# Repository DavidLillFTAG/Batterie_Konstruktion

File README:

Testfile
<<<<<<< HEAD
123456

=======
123
123123
>>>>>>> dev_david

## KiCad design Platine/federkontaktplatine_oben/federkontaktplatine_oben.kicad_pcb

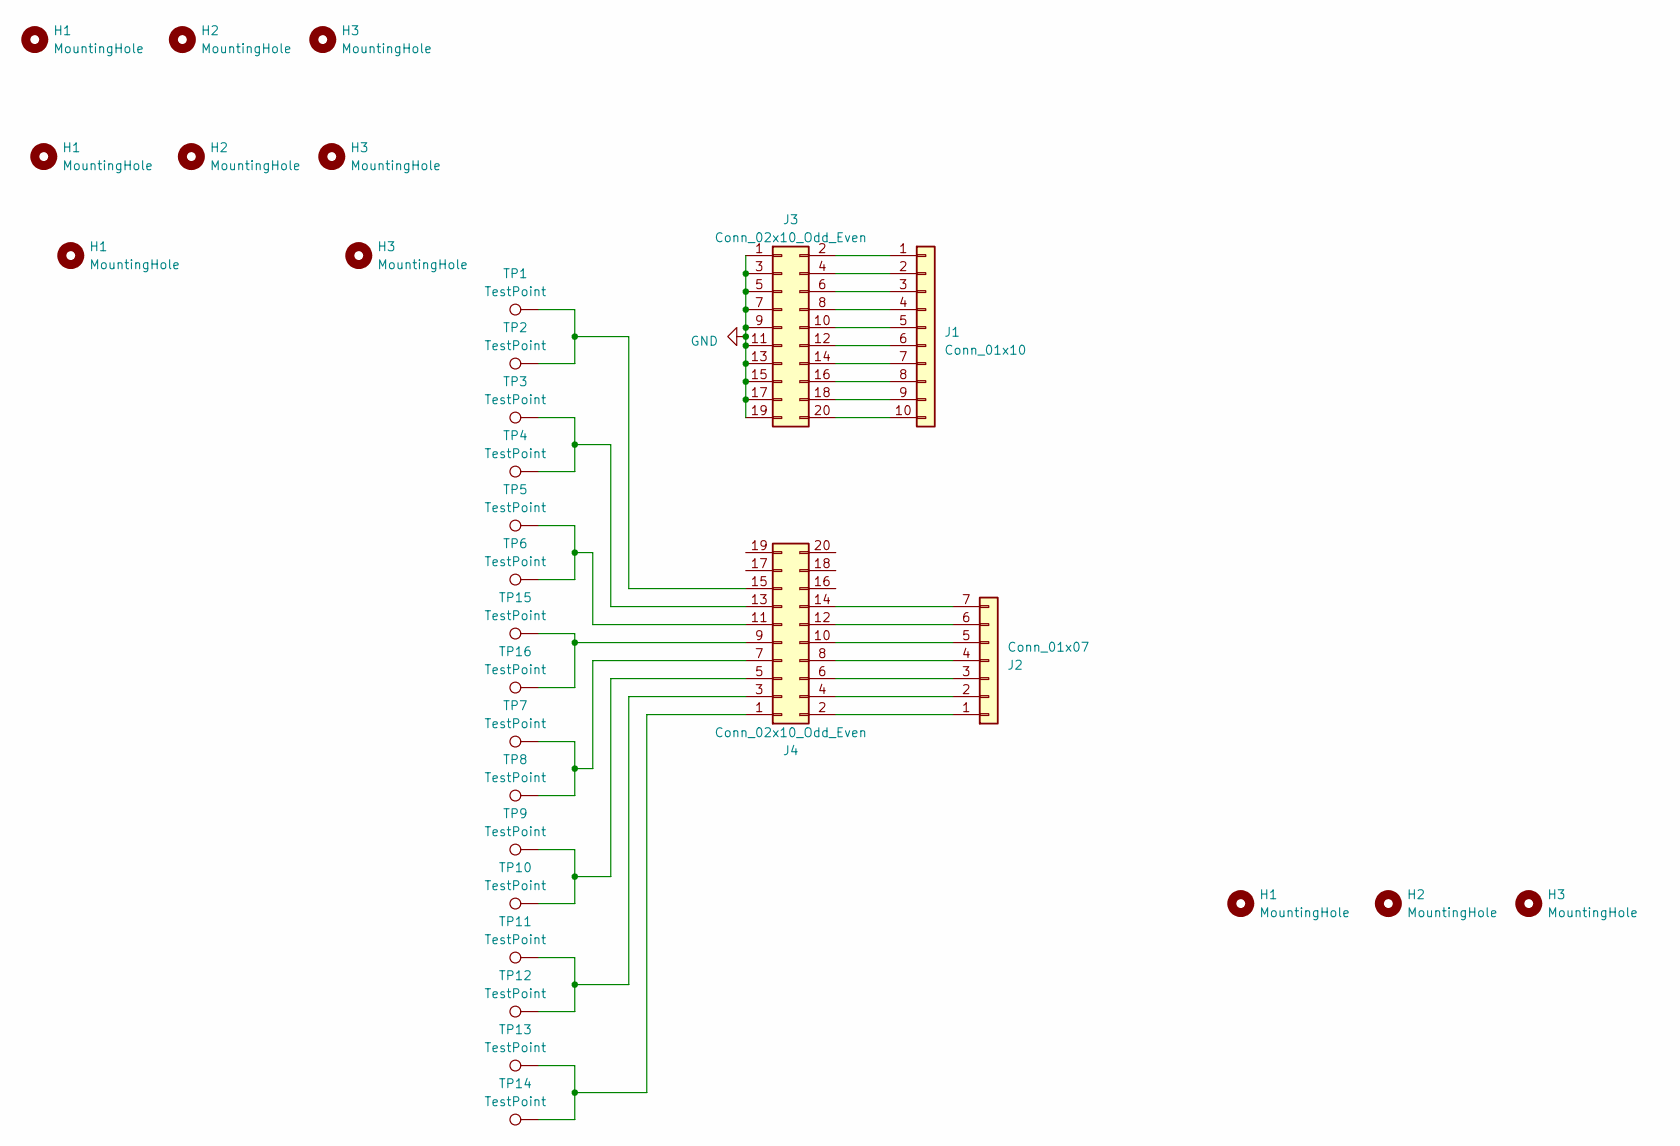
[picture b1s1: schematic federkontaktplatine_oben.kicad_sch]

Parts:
H1, H2, H3: MountingHole; MountingHole_3.2mm_M3_DIN965
J1: Conn_01x10; MOLEX_436501012
J2: Conn_01x07; MOLEX_436500712
J3, J4: Conn_02x10_Odd_Even; PinSocket_2x10_P2.54mm_Vertical_SMD
TP1, TP2, TP3, TP4, TP5, TP6, TP7, TP8, TP9, TP10, TP11, TP12, TP13, TP14, TP15, TP16: TestPoint; PAD_1x2mm

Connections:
GND: J3.1, J3.3, J3.5, J3.7, J3.9, J3.11, J3.13, J3.15, J3.17, J3.19
unnamed: J1.1, J3.2
unnamed: J1.2, J3.4
unnamed: J1.3, J3.6
unnamed: J1.4, J3.8
unnamed: J1.5, J3.10
unnamed: J1.6, J3.12
unnamed: J1.7, J3.14
unnamed: J1.8, J3.16
unnamed: J1.9, J3.18
unnamed: J1.10, J3.20
unnamed: J2.1, J4.2
unnamed: J2.2, J4.4
unnamed: J2.3, J4.6
unnamed: J2.4, J4.8
unnamed: J2.5, J4.10
unnamed: J2.6, J4.12
unnamed: J2.7, J4.14
unnamed: J4.1, TP13.1, TP14.1
unnamed: J4.3, TP11.1, TP12.1
unnamed: J4.5, TP9.1, TP10.1
unnamed: J4.7, TP7.1, TP8.1
unnamed: J4.9, TP15.1, TP16.1
unnamed: J4.11, TP5.1, TP6.1
unnamed: J4.13, TP3.1, TP4.1
unnamed: J4.15, TP1.1, TP2.1

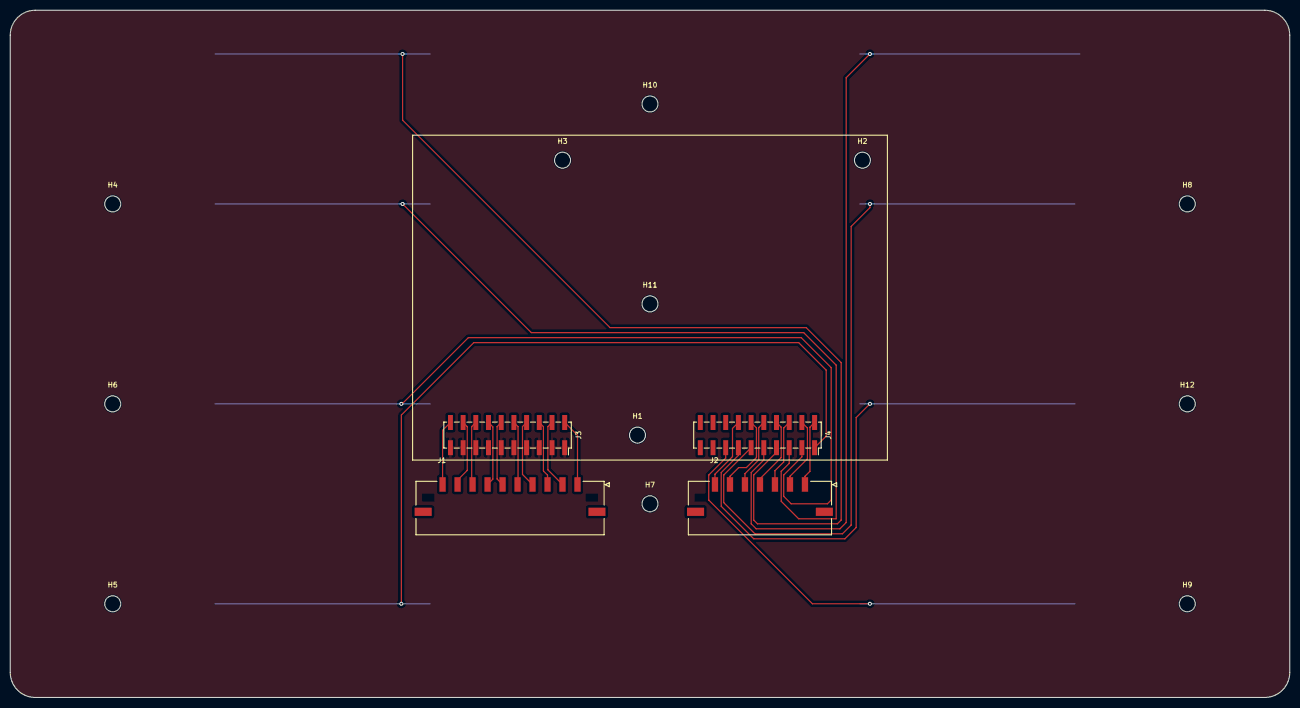
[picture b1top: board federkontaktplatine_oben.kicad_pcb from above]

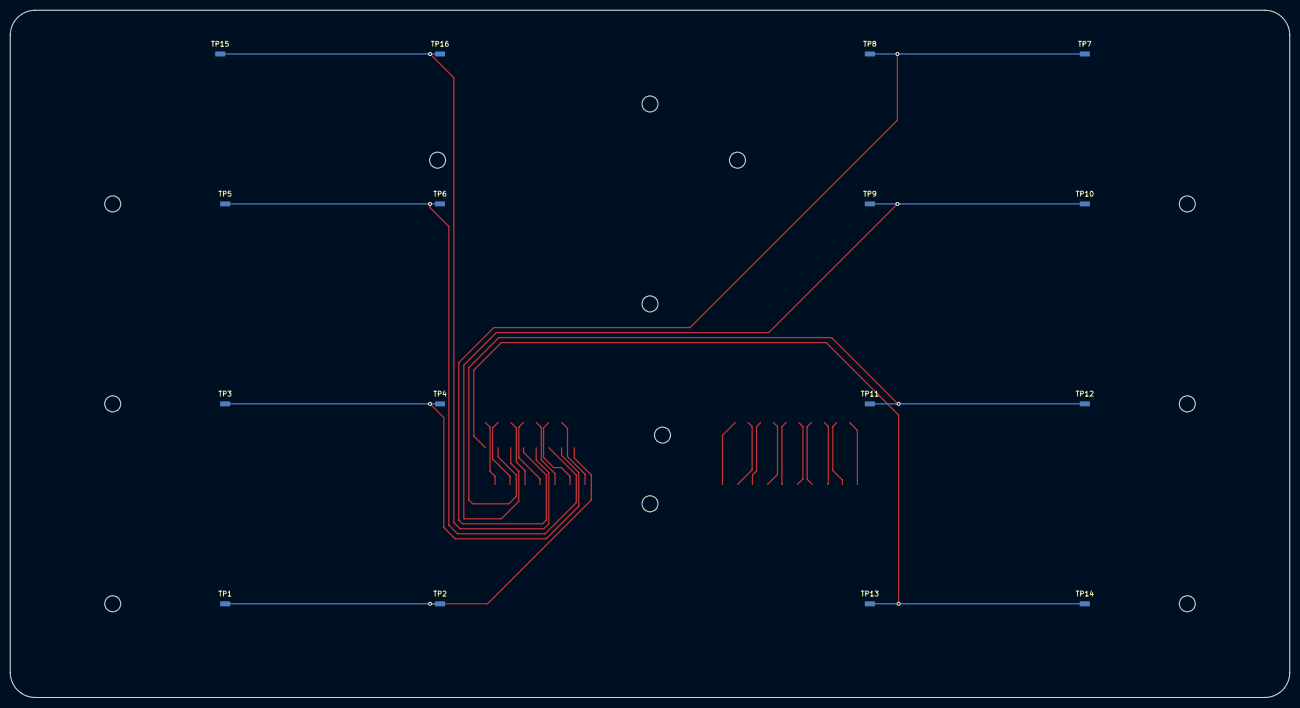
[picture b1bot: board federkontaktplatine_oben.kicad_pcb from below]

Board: 2 copper layers, 256.0 x 137.5 mm, 32 parts (16 on the bottom side), 26 nets.

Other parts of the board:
H4, H5, H6, H7, H8, H9, H10, H11, H12: MountingHole; MountingHole_3.2mm_M3_DIN965

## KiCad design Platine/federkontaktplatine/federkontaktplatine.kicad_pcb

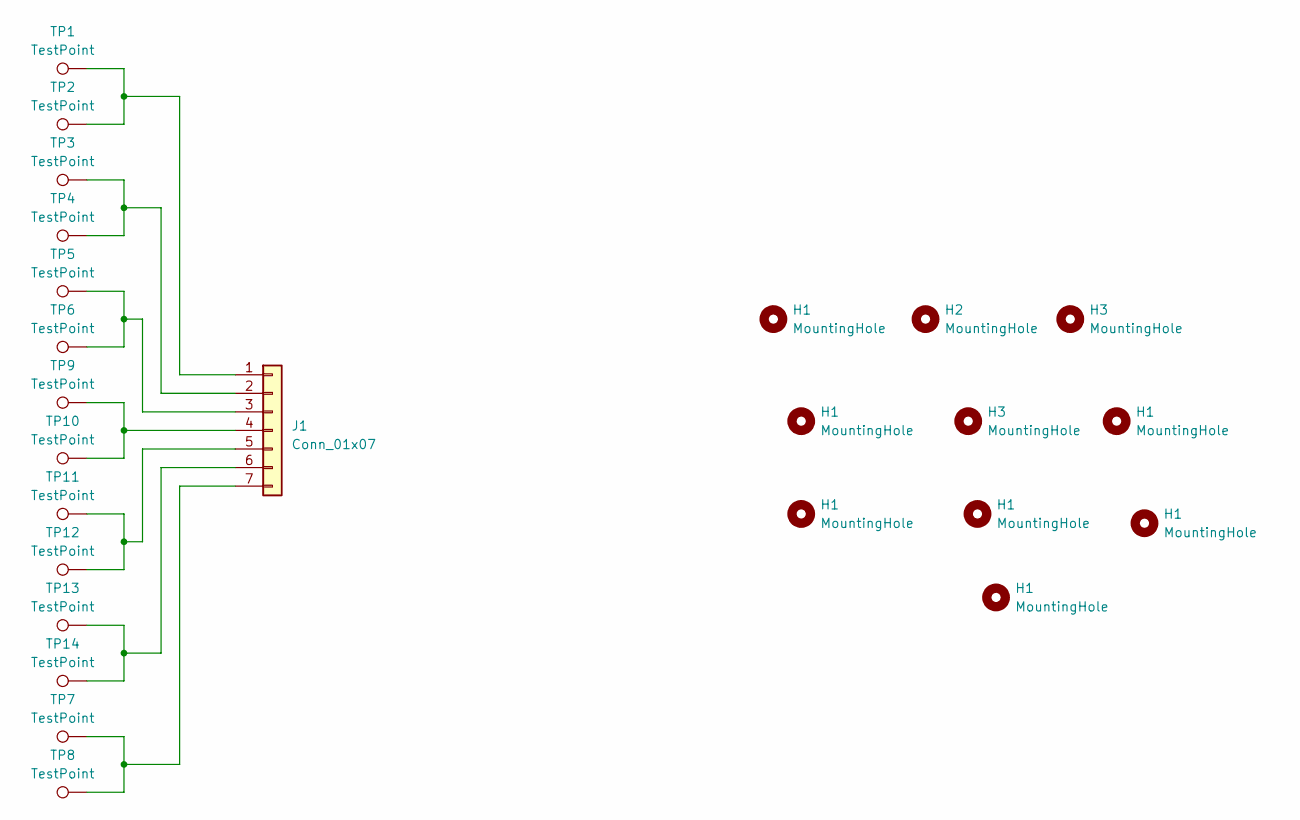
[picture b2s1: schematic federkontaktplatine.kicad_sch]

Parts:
H1, H2, H3: MountingHole; MountingHole_3.2mm_M3_DIN965
J1: Conn_01x07; Molex_Micro-Fit_3.0_43650-0724_1x07-1MP_P3.00mm_Vertical
TP1, TP2, TP3, TP4, TP5, TP6, TP7, TP8, TP9, TP10, TP11, TP12, TP13, TP14: TestPoint; PAD_1x2mm

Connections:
unnamed: J1.1, TP1.1, TP2.1
unnamed: J1.2, TP3.1, TP4.1
unnamed: J1.3, TP5.1, TP6.1
unnamed: J1.4, TP9.1, TP10.1
unnamed: J1.5, TP11.1, TP12.1
unnamed: J1.6, TP13.1, TP14.1
unnamed: J1.7, TP7.1, TP8.1

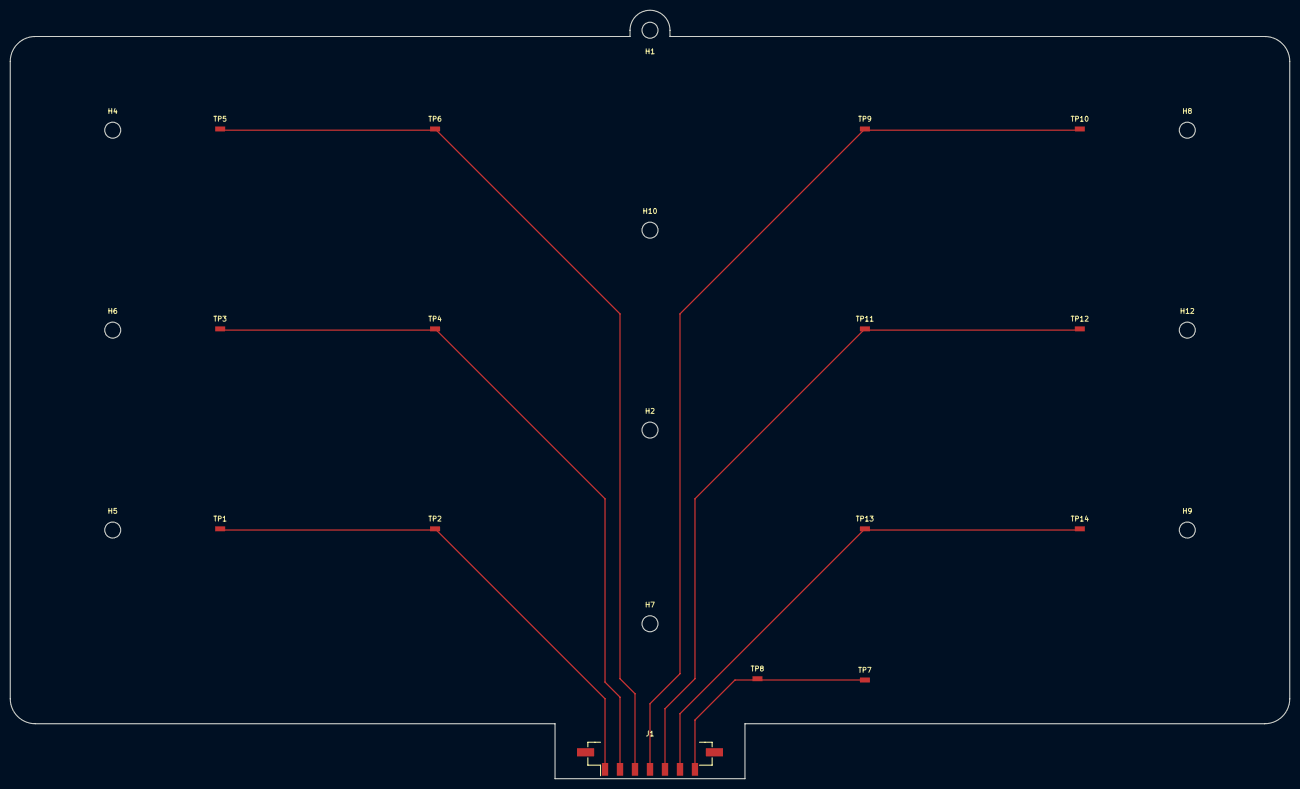
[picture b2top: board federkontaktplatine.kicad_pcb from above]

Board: 2 copper layers, 256.0 x 153.8 mm, 25 parts (0 on the bottom side), 7 nets.

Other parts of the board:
H4, H5, H6, H7, H8, H9, H10, H12: MountingHole; MountingHole_3.2mm_M3_DIN965

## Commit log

2025-03-31 Create README
    readme
2025-03-31 Upload von Konstruktion
2025-04-15 Update Konstruktion
2025-04-22 Kabelschuh
2025-04-22 test
2025-04-22 test commit
2025-04-23 test1
2025-04-23 Umstrukturierung POM
2025-05-07 redesign
2025-05-08 punktschweißkonstruktion v1
2025-05-12 weiteres design...
2025-05-12 .stp erstellt
2025-05-14 Packkontakte hinzugefügt
2025-05-14 Runde kontakte
2025-05-14 Revert "test"
    This reverts commit b9fee8c553567fd31c1f79eb58c88e24752093f0.
2025-05-15 Platine oben hinzugefügt
2025-05-19 doku anfang
2025-05-21 fehler beheben
2025-05-22 Platinen überarbeitet
2025-05-22 Nickelformen überarbeitet
2025-05-23 Platinen update
2025-05-23 löcher in kupferplatten auf 10,2mm verbreitert
2025-05-25 montagelöcher und aufnahme für BMS
2025-05-25 backup commit
2025-05-25 removed CAD from platinenzweig
2025-05-25 removed pcb data from cad
2025-05-25 moved doku to overleaf
2025-05-25 removed doku
2025-05-26 montagepunkte untere platine
2025-05-26 montage für untere platine + ausschnitte in kupferplatten
2025-05-27 montagelöcher untere platte
2025-05-27 untere platte rundung für fertigung und export von neuen kupferplatten
2025-05-27 kupferplatten update
2025-05-27 federplatine oben montagelöcher
2025-05-27 platinen
2025-05-28 platinen aus Platinenzweig geholt
2025-05-28 kleines update
2025-05-28 Kabelstrang
2025-06-04 platinen gerber
2025-06-04 platinen step dateien aus baugruppe entfernt
2025-06-17 stanzwerkzeug, platte unten, ...
2025-06-17 platine unten in CAD
